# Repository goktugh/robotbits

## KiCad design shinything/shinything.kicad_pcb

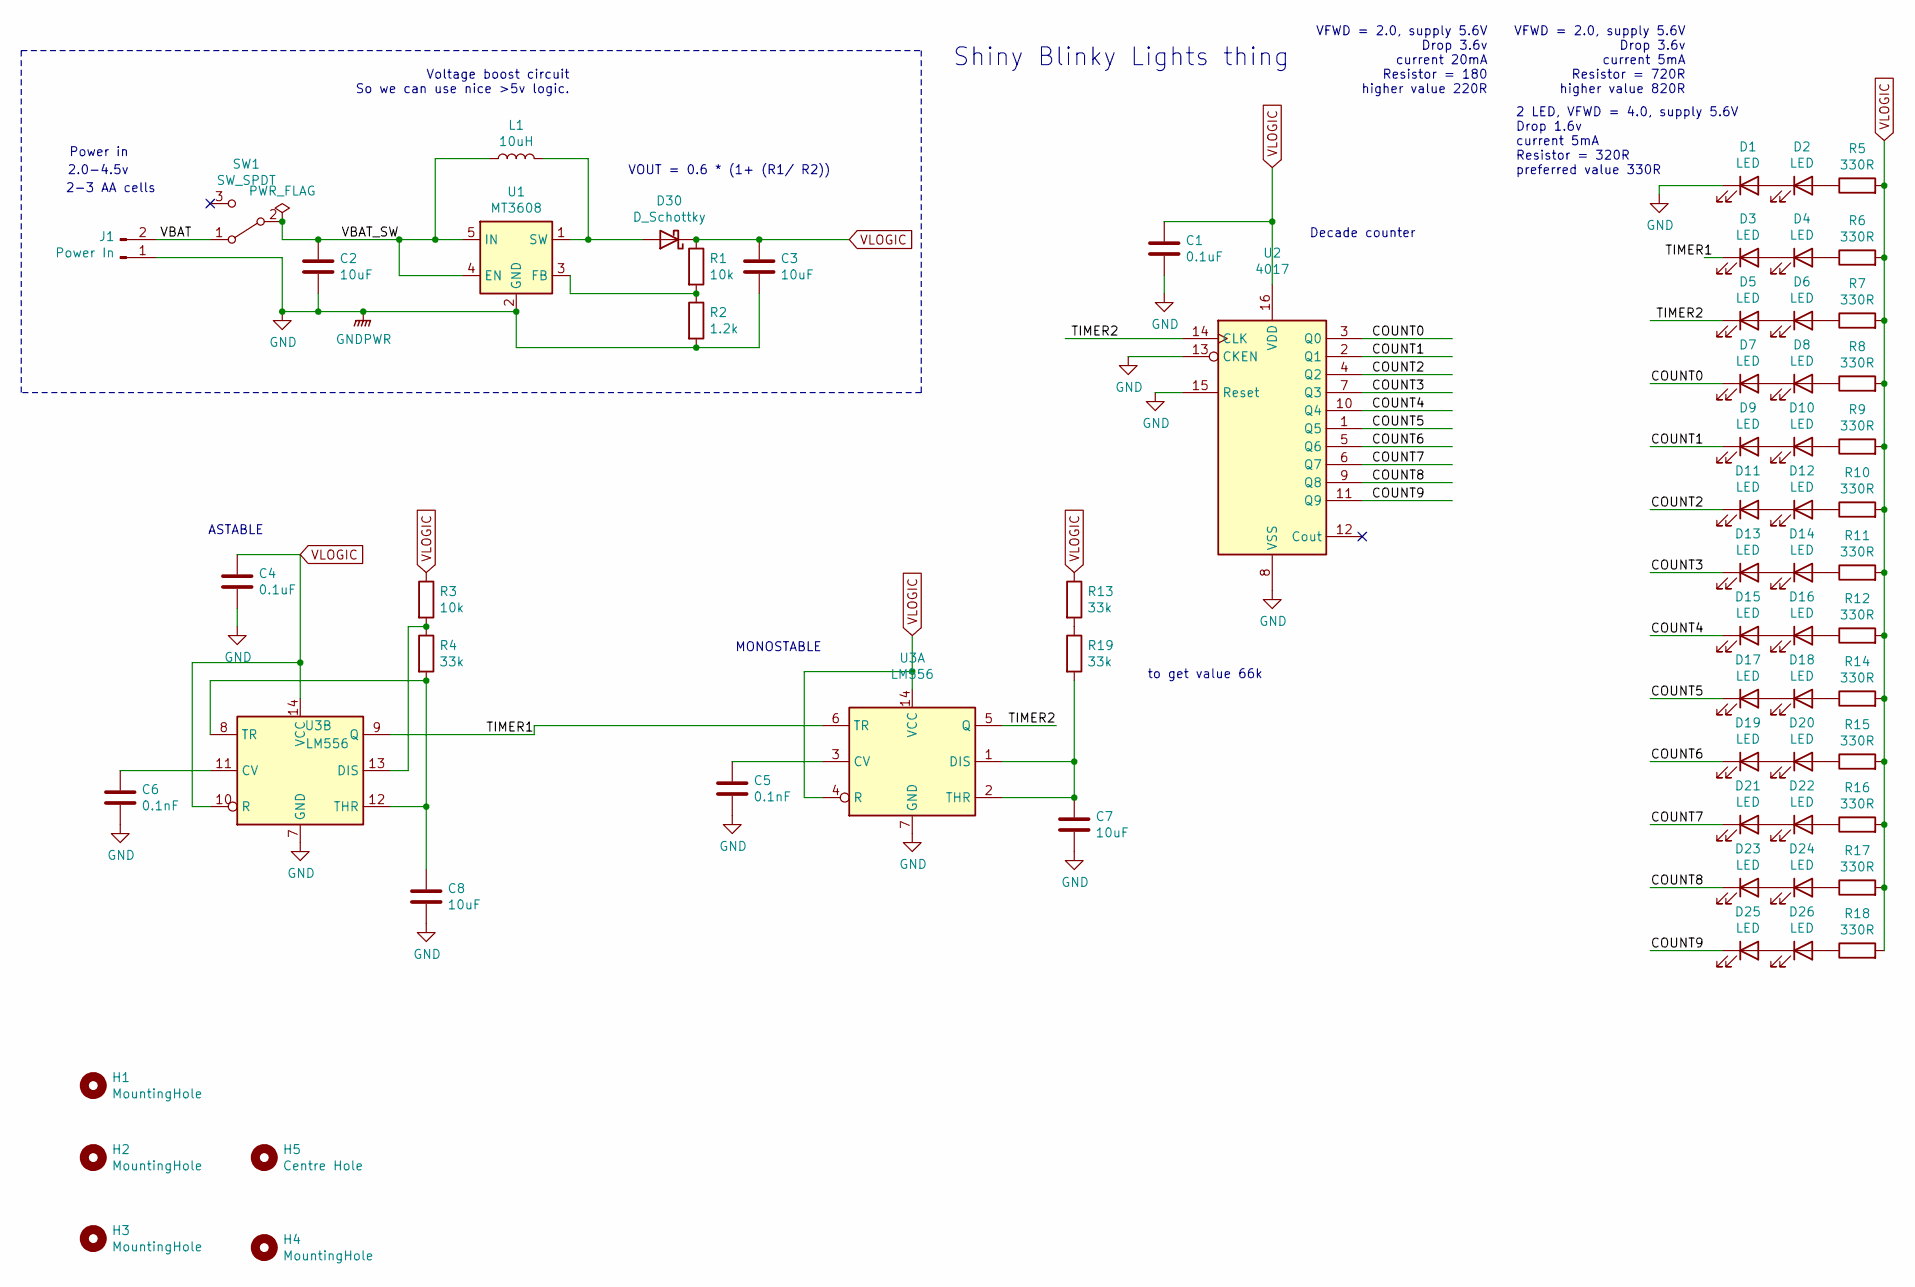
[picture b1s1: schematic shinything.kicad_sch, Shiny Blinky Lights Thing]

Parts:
C1, C4: 0.1uF; C_1206_3216Metric; LCSC C107179
C2, C3, C7, C8: 10uF; C_1206_3216Metric; LCSC C47971
C5, C6: 0.1nF; C_1206_3216Metric; LCSC C24497
D1, D2, D3, D4, D5, D6, D7, D8, D9, D10, D11, D12, D13, D14, D15, D16, D17, D18, D19, D20, D21, D22, D23, D24, D25, D26: LED; LED_1206_3216Metric_Castellated; LCSC C125086
D30: D_Schottky; D_SMA_Handsoldering; LCSC C232829
H1, H2, H3, H4: MountingHole; MountingHole_2.5mm
H5: Centre Hole; MountingHole_2.5mm
J1: Power In; SolderWire-1sqmm_1x02_P5.4mm_D1.4mm_OD2.7mm
L1: 10uH; L_1210_3225Metric_Pad1.42x2.65mm_HandSolder; LCSC C464437
R1, R3: 10k; R_0805_2012Metric; LCSC C100047
R2: 1.2k; R_0805_2012Metric; LCSC C114526
R4, R13, R19: 33k; R_0805_2012Metric; LCSC C137446
R5, R6, R7, R8, R9, R10, R11, R12, R14, R15, R16, R17, R18: 330R; R_0805_2012Metric; LCSC C105877
SW1: SW_SPDT; PinSocket_1x03_P2.54mm_Vertical; LCSC C92657
U1: MT3608; SOT-23-6; LCSC C84817
U2: 4017; SOIC-16_3.9x9.9mm_P1.27mm; LCSC C11349
U3: LM556; SOIC-14_3.9x8.7mm_P1.27mm; LCSC C434479

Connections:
/COUNT0: D7.1 (K), U2.3 (Q0)
/COUNT1: D9.1 (K), U2.2 (Q1)
/COUNT2: D11.1 (K), U2.4 (Q2)
/COUNT3: D13.1 (K), U2.7 (Q3)
/COUNT4: D15.1 (K), U2.10 (Q4)
/COUNT5: D17.1 (K), U2.1 (Q5)
/COUNT6: D19.1 (K), U2.5 (Q6)
/COUNT7: D21.1 (K), U2.6 (Q7)
/COUNT8: D23.1 (K), U2.9 (Q8)
/COUNT9: D25.1 (K), U2.11 (Q9)
/TIMER1: D3.1 (K), U3.6 (TR), U3.9 (Q)
/TIMER2: D5.1 (K), U2.14 (CLK), U3.5 (Q)
/VBAT: J1.2, SW1.1 (A)
/VBAT_SW: C2.1, L1.1, SW1.2 (B), U1.4 (EN), U1.5 (IN)
GND: C1.2, C2.2, C3.2, C4.2, C5.2, C6.2, C7.2, C8.2, D1.1 (K), J1.1, R2.2, U1.2 (GND), U2.8 (VSS), U2.13 (CKEN), U2.15 (Reset), U3.7 (GND)
unnamed: C5.1, U3.3 (CV)
unnamed: C6.1, U3.11 (CV)
unnamed: C7.1, R19.2, U3.1 (DIS), U3.2 (THR)
unnamed: C8.1, R4.2, U3.8 (TR), U3.12 (THR)
unnamed: D1.2 (A), D2.1 (K)
unnamed: D2.2 (A), R5.1
unnamed: D3.2 (A), D4.1 (K)
unnamed: D4.2 (A), R6.1
unnamed: D5.2 (A), D6.1 (K)
unnamed: D6.2 (A), R7.1
unnamed: D7.2 (A), D8.1 (K)
unnamed: D8.2 (A), R8.1
unnamed: D9.2 (A), D10.1 (K)
unnamed: D10.2 (A), R9.1
unnamed: D11.2 (A), D12.1 (K)
unnamed: D12.2 (A), R10.1
unnamed: D13.2 (A), D14.1 (K)
unnamed: D14.2 (A), R11.1
unnamed: D15.2 (A), D16.1 (K)
unnamed: D16.2 (A), R12.1
unnamed: D17.2 (A), D18.1 (K)
unnamed: D18.2 (A), R14.1
unnamed: D19.2 (A), D20.1 (K)
unnamed: D20.2 (A), R15.1
unnamed: D21.2 (A), D22.1 (K)
unnamed: D22.2 (A), R16.1
unnamed: D23.2 (A), D24.1 (K)
unnamed: D24.2 (A), R17.1
unnamed: D25.2 (A), D26.1 (K)
unnamed: D26.2 (A), R18.1
unnamed: D30.2 (A), L1.2, U1.1 (SW)
unnamed: R1.2, R2.1, U1.3 (FB)
unnamed: R3.2, R4.1, U3.13 (DIS)
unnamed: R13.2, R19.1
VLOGIC: C1.1, C3.1, C4.1, D30.1 (K), R1.1, R3.1, R5.2, R6.2, R7.2, R8.2, R9.2, R10.2, R11.2, R12.2, R13.1, R14.2, R15.2, R16.2, R17.2, R18.2, U2.16 (VDD), U3.4 (R), U3.10 (R), U3.14 (VCC)

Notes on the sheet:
Power in
2.0-4.5v
2-3 AA cells
ASTABLE
Voltage boost circuit So we can use nice >5v logic.
MONOSTABLE
VOUT = 0.6 * (1+ (R1/ R2))
to get value 66k
Shiny Blinky Lights thing
Decade counter
VFWD = 2.0, supply 5.6V Drop 3.6v current 20mA Resistor = 180 higher value 220R
2 LED, VFWD = 4.0, supply 5.6V Drop 1.6v current 5mA Resistor = 320R preferred value 330R
VFWD = 2.0, supply 5.6V Drop 3.6v current 5mA Resistor = 720R higher value 820R

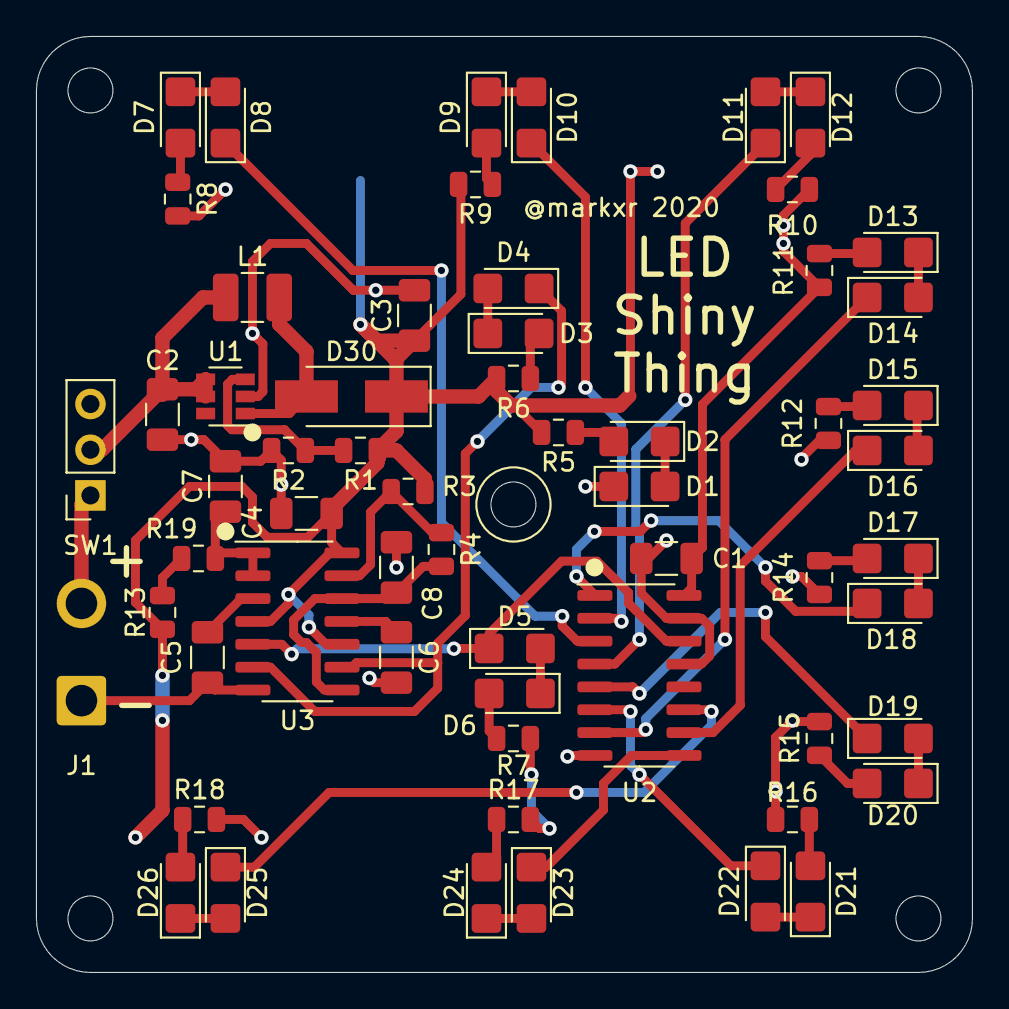
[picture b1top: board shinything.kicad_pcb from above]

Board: 2 copper layers, 52.0 x 52.0 mm, 65 parts (0 on the bottom side), 50 nets.

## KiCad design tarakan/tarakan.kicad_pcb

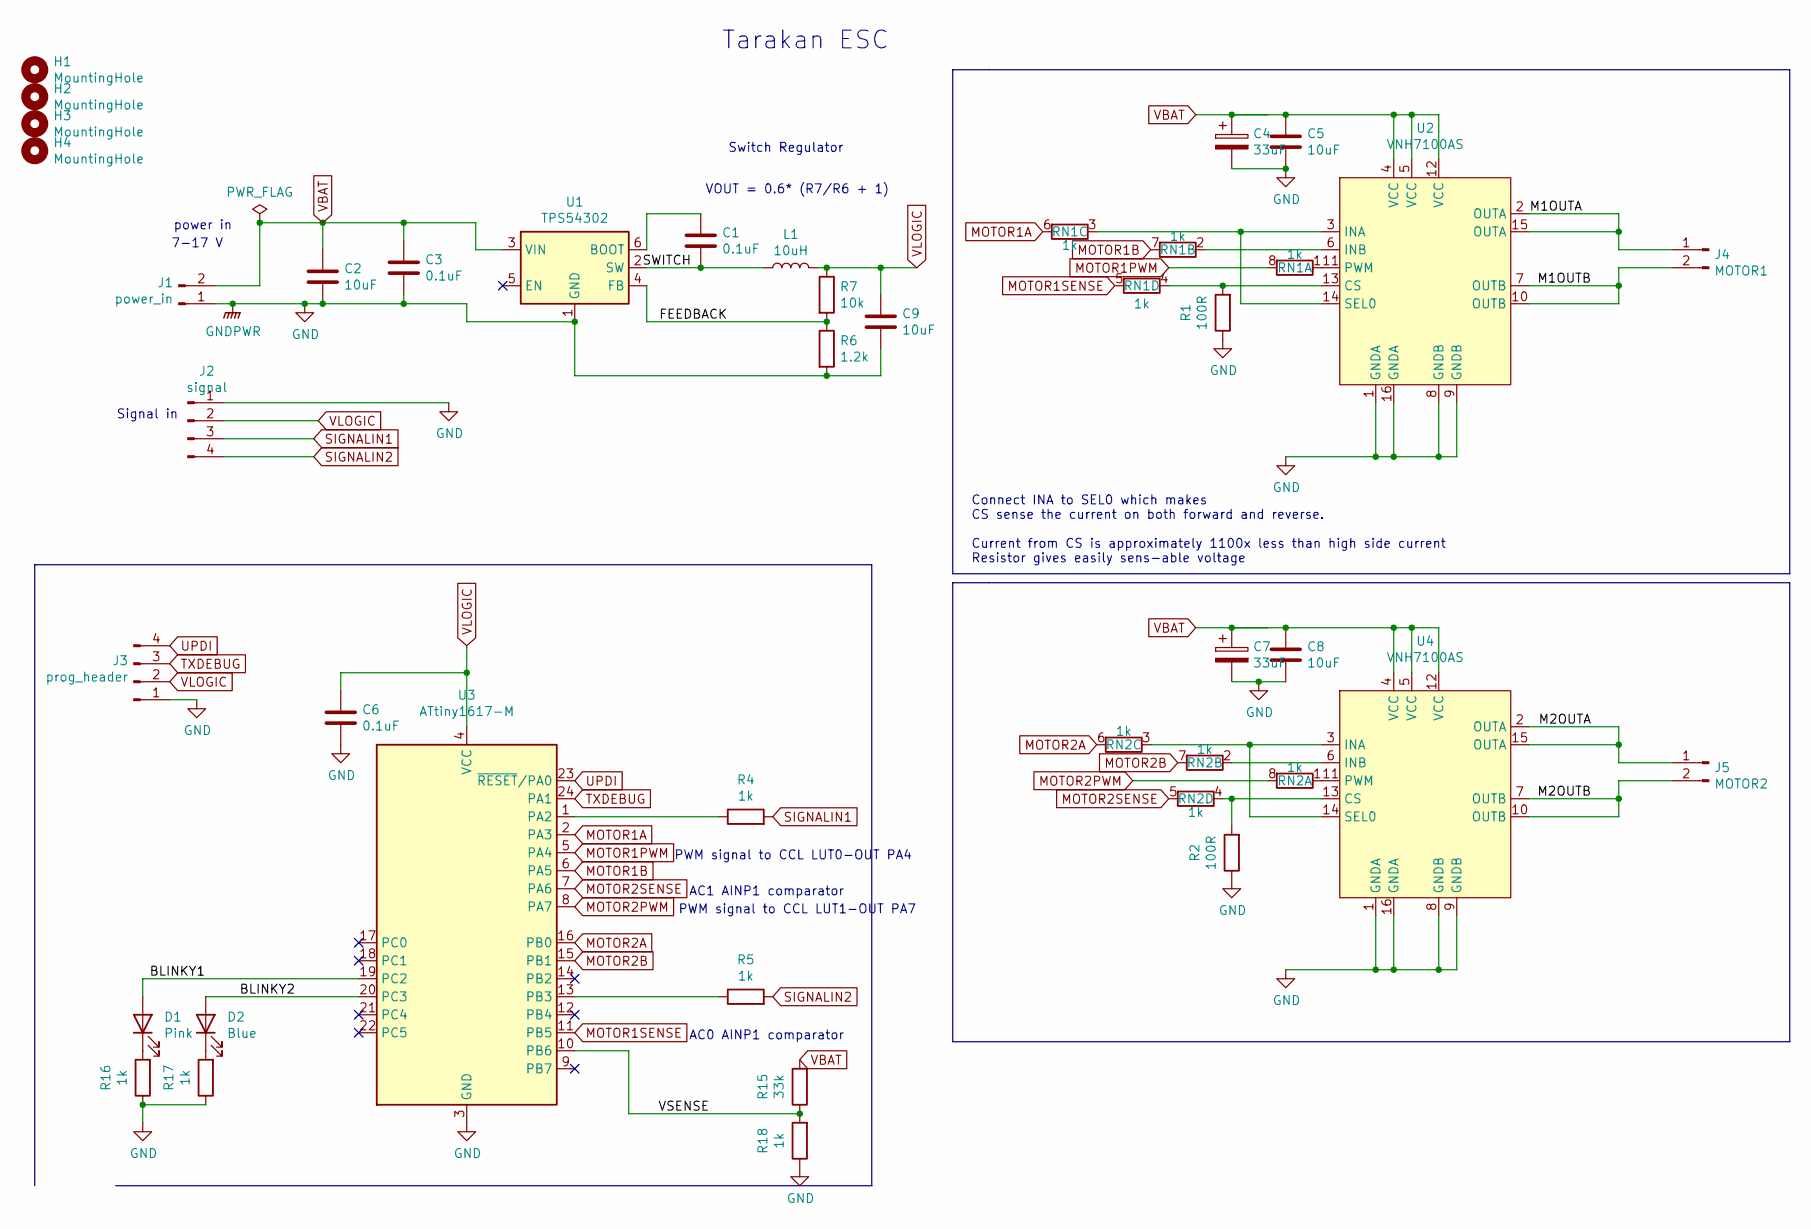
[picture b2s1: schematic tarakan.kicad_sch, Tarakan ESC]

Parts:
C1, C3, C6: 0.1uF; C_1206_3216Metric
C2, C5, C8, C9: 10uF; C_1210_3225Metric
C4, C7: 33uF; CP_Elec_6.3x7.7; part panasonic EEE1HA330XP
D1: Pink; LED_1206_3216Metric_Castellated
D2: Blue; LED_1206_3216Metric_Castellated
H1, H2, H3, H4: MountingHole; MountingHole_2.5mm
J1: power_in; SolderWirePad_1x02_P7.62mm_Drill2mm
J2: signal; PinHeader_1x04_P2.54mm_Vertical
J3: prog_header; PinSocket_1x04_P2.00mm_Vertical
J4: MOTOR1; wirepads_motor
J5: MOTOR2; wirepads_motor
L1: 10uH; L_6.3x6.3_H3
R1, R2: 100R; R_0805_2012Metric
R4, R5, R16, R17, R18: 1k; R_0805_2012Metric
R6: 1.2k; R_0805_2012Metric
R7: 10k; R_0805_2012Metric
R15: 33k; R_0805_2012Metric
RN1, RN2: 1k; R_Array_Convex_4x0603
U1: TPS54302; SOT-23-6
U2, U4: VNH7100AS; SOIC-16_3.9x9.9mm_P1.27mm
U3: ATtiny1617-M; QFN-24-1EP_4x4mm_P0.5mm_EP2.6x2.6mm

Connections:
/BLINKY1: D1.2 (A), U3.19 (PC2)
/BLINKY2: D2.2 (A), U3.20 (PC3)
/FEEDBACK: R6.1, R7.2, U1.4 (FB)
/M1OUTA: J4.1, U2.2 (OUTA), U2.15 (OUTA)
/M1OUTB: J4.2, U2.7 (OUTB), U2.10 (OUTB)
/M2OUTA: J5.1, U4.2 (OUTA), U4.15 (OUTA)
/M2OUTB: J5.2, U4.7 (OUTB), U4.10 (OUTB)
/SWITCH: C1.2, L1.1, U1.2 (SW)
/VSENSE: R15.1, R18.2, U3.10 (PB6)
GND: C2.2, C3.2, C4.2, C5.2, C6.2, C7.2, C8.2, C9.2, J1.1, J2.1, J3.1, R1.1, R2.1, R6.2, R16.1, R17.1, R18.1, U1.1 (GND), U2.1 (GNDA), U2.8 (GNDB), U2.9 (GNDB), U2.16 (GNDA), U3.3 (GND), U3.25 (GND), U4.1 (GNDA), U4.8 (GNDB), U4.9 (GNDB), U4.16 (GNDA)
MOTOR1A: RN1.6 (R3.2), U3.2 (PA3)
MOTOR1B: RN1.7 (R2.2), U3.6 (PA5)
MOTOR1PWM: RN1.8 (R1.2), U3.5 (PA4)
MOTOR1SENSE: RN1.5 (R4.2), U3.11 (PB5)
MOTOR2A: RN2.6 (R3.2), U3.16 (PB0)
MOTOR2B: RN2.7 (R2.2), U3.15 (PB1)
MOTOR2PWM: RN2.8 (R1.2), U3.8 (PA7)
MOTOR2SENSE: RN2.5 (R4.2), U3.7 (PA6)
unnamed: C1.1, U1.6 (BOOT)
unnamed: D1.1 (K), R16.2
unnamed: D2.1 (K), R17.2
unnamed: R1.2, RN1.4 (R4.1), U2.13 (CS)
unnamed: R2.2, RN2.4 (R4.1), U4.13 (CS)
unnamed: R4.1, U3.1 (PA2)
unnamed: R5.1, U3.13 (PB3)
unnamed: RN1.1 (R1.1), U2.11 (PWM)
unnamed: RN1.2 (R2.1), U2.6 (INB)
unnamed: RN1.3 (R3.1), U2.3 (INA), U2.14 (SEL0)
unnamed: RN2.1 (R1.1), U4.11 (PWM)
unnamed: RN2.2 (R2.1), U4.6 (INB)
unnamed: RN2.3 (R3.1), U4.3 (INA), U4.14 (SEL0)
SIGNALIN1: J2.3, R4.2
SIGNALIN2: J2.4, R5.2
TXDEBUG: J3.3, U3.24 (PA1)
UPDI: J3.4, U3.23 (~RESET~/PA0)
VBAT: C2.1, C3.1, C4.1, C5.1, C7.1, C8.1, J1.2, R15.2, U1.3 (VIN), U2.4 (VCC), U2.5 (VCC), U2.12 (VCC), U4.4 (VCC), U4.5 (VCC), U4.12 (VCC)
VLOGIC: C6.1, C9.1, J2.2, J3.2, L1.2, R7.1, U3.4 (VCC)

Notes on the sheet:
Signal in
7-17 V
power in
PWM signal to CCL LUT0-OUT PA4
Switch Regulator
AC1 AINP1 comparator
AC0 AINP1 comparator
Tarakan ESC
VOUT = 0.6* (R7/R6 + 1)
PWM signal to CCL LUT1-OUT PA7
Connect INA to SEL0 which makes CS sense the current on both forward and reverse. Current from CS is approximately 1100x less than high side current Resistor gives easily sens-able voltage

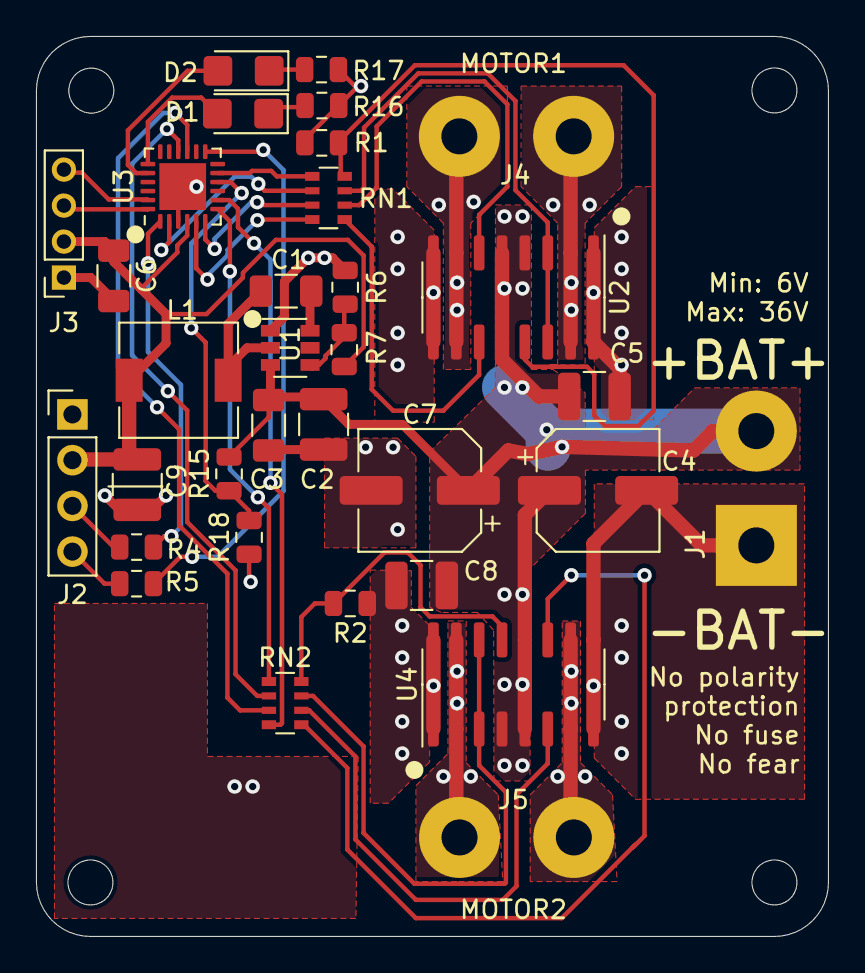
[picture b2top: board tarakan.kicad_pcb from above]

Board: 2 copper layers, 44.0 x 50.0 mm, 37 parts (0 on the bottom side), 37 nets.
